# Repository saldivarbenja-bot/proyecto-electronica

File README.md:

# Sistema de Adquisicion y Acondicionamiento de Senales EMG

## Descripcion del proyecto

Este repositorio contiene el diseno de hardware y los archivos de fabricacion desarrollados para el proyecto de adquisicion de senales electromiograficas (EMG) de superficie. El objetivo es tomar los potenciales electricos generados por la actividad muscular, amplificarlos, filtrarlos mediante un circuito analogico y acondicionarlos para su posterior lectura segura mediante el convertidor analogo-digital (ADC) de un microcontrolador.

### Contexto y cambios respecto a la primera entrega

En la primera etapa del curso probamos el circuito en una protoboard. Aunque logramos captar senal, el montaje era muy inestable: los cables sueltos captaban demasiado ruido de 50 Hz de la red electrica y cualquier movimiento generaba falsos contactos o artefactos en la lectura.

Para esta segunda entrega trasladamos el circuito a una placa de circuito impreso (PCB) de una sola cara (capa inferior B.Cu), pensada para fabricarse mediante ruteo CNC en el laboratorio. Tambien anadimos zocalos y borneras para montar los componentes con firmeza y alimentar todo con dos baterias de 9V, lo que elimina el ruido de la red y previene riesgos electricos.

## Integrantes del grupo (Grupo 5)

* Marcelo de la Fuente (ma.delafuente@udd.cl)
* Benjamin Saldivar (b.saldivarb@udd.cl)
* Manuel Sepulveda (ma.sepulvedar@udd.cl)

Curso: Electronica Biomedica - Seccion 1
Carrera: Ingenieria Civil en Biomedicina
Universidad del Desarrollo

## Descripcion del circuito y componentes

El sistema cuenta con las siguientes etapas:

1. Captacion: Sensores de superficie conectados a un modulo Muscle Sensor V3 (o etapa equivalente de instrumentacion) que toma la diferencia de potencial muscular y atenua el ruido comun.
2. Acondicionamiento analogico: Dos amplificadores operacionales LM741 alimentados con fuente simetrica (+9V / -9V) encargados de ajustar la fase y la ganancia mediante resistencias de 15k, 8.2k y 10k ohmios.
3. Proteccion de entrada al microcontrolador: Un divisor de tension resistivo (18k y 10k ohmios) que reduce la salida maxima de 9V a menos de 3.3V, evitando sobrevoltajes en el microcontrolador.
4. Integracion con microcontrolador: Tiras de pines para montar una placa de desarrollo ESP32-S3 de 38 pines y facilitar la conexion de la senal acondicionada al ADC.
5. Alimentacion aislada: Dos baterias de 9V conectadas mediante borneras para generar +9V, -9V y tierra (GND).

### Lista de materiales

| Cantidad | Componente | Funcion | Encapsulado / Conexion |
| --- | --- | --- | --- |
| 1 | Modulo Advancer Muscle Sensor V3 | Captacion y pre-amplificacion EMG | Tira de pines hembra de 1x5 |
| 2 | Amplificadores operacionales LM741 | Inversion y ajuste de ganancia | DIP-8 con zocalo |
| 1 | ESP32-S3 (38 pines) | Socket de montaje | Dos tiras de pines de 1x19 |
| 4 | Resistencias de ganancia | Ajuste de ganancia (15k, 8.2k y dos de 10k) | Resistencias axiales Through-Hole |
| 2 | Resistencias divisor | Escalado a rango de 3.3V (18k y 10k) | Resistencias axiales Through-Hole |
| 2 | Borneras de 2 pines (5.08 mm) | Entrada de alimentacion desde baterias de 9V | Montaje en placa Through-Hole |

## Reglas de diseno de la placa (KiCad / CNC)

El ruteo de la placa se realizo respetando las limitaciones de fabricacion de la fresadora CNC del laboratorio:

* Capa de cobre: Ruteo realizado exclusivamente en la cara inferior (B.Cu).
* Ancho de pista minimo: 0.8 mm.
* Espaciado entre pistas (Clearance): 0.8 mm.
* Borde de la placa: Delimitado en la capa Edge.Cuts.
* Montaje: 4 perforaciones de 3.2 mm de diametro en las esquinas para fijar la placa.
* Serigrafia: Indicaciones claras para la polaridad de las baterias (+9V, GND, -9V), pin 1 de los circuitos integrados y nombres de conectores.

## Estructura de carpetas

El repositorio esta organizado de la siguiente manera:

```
├── README.md                      # Descripcion general del proyecto
├── docs/                          # Hojas de datos e informes de entrega
│   ├── datasheets/
│   └── entregables/
└── electronica/                   # Diseno esquematico y PCB
    ├── kicad/                     # Proyecto en KiCad (.kicad_pro, .kicad_sch, .kicad_pcb)
    ├── libraries/                 # Simbolos, huellas y modelos 3D locales
    └── outputs/                   # Archivos para fabricacion y revision
        ├── gerbers/               # Archivos Gerber y de perforacion (.zip)
        ├── schematic.pdf          # Esquema electronico en PDF
        ├── pcb_views/             # Vistas de pistas, render 3D y reporte DRC
        └── BOM.csv                # Lista de materiales exportada
```

## Como abrir y revisar el proyecto

### Abrir esquematicos y PCB en KiCad

1. Clona el repositorio o descarga el archivo ZIP:
   ```
   git clone <URL_DEL_REPOSITORIO>
   ```
2. Abre KiCad (version 7 o superior).
3. Ve a `Archivo > Abrir Proyecto` y selecciona el archivo `.kicad_pro` dentro de `electronica/kicad/`.
4. Las librerias de componentes y huellas estan guardadas de forma local en la carpeta `electronica/libraries/`, por lo que no presentaran dependencias externas faltantes.

## Referencias

* Informacion del sensor EMG: [Tutorial Sensor EMG - UNIT Electronics](https://blog.uelectronics.com/electronica/sensor-emg-tutorial-completo/)
* Circuito de ejemplo: [DIY Muscle Sensor / EMG Circuit - Instructables](https://www.instructables.com/Muscle-EMG-Sensor-for-a-Microcontroller/)
* Proyectos abiertos de referencia: [BioAmp EXG Pill](https://github.com/upsidedownlabs/BioAmp-EXG-Pill) y [Shield EKG-EMG de OLIMEX](https://www.olimex.com/Products/Duino/Shields/SHIELD-EKG-EMG/open-source-hardware)

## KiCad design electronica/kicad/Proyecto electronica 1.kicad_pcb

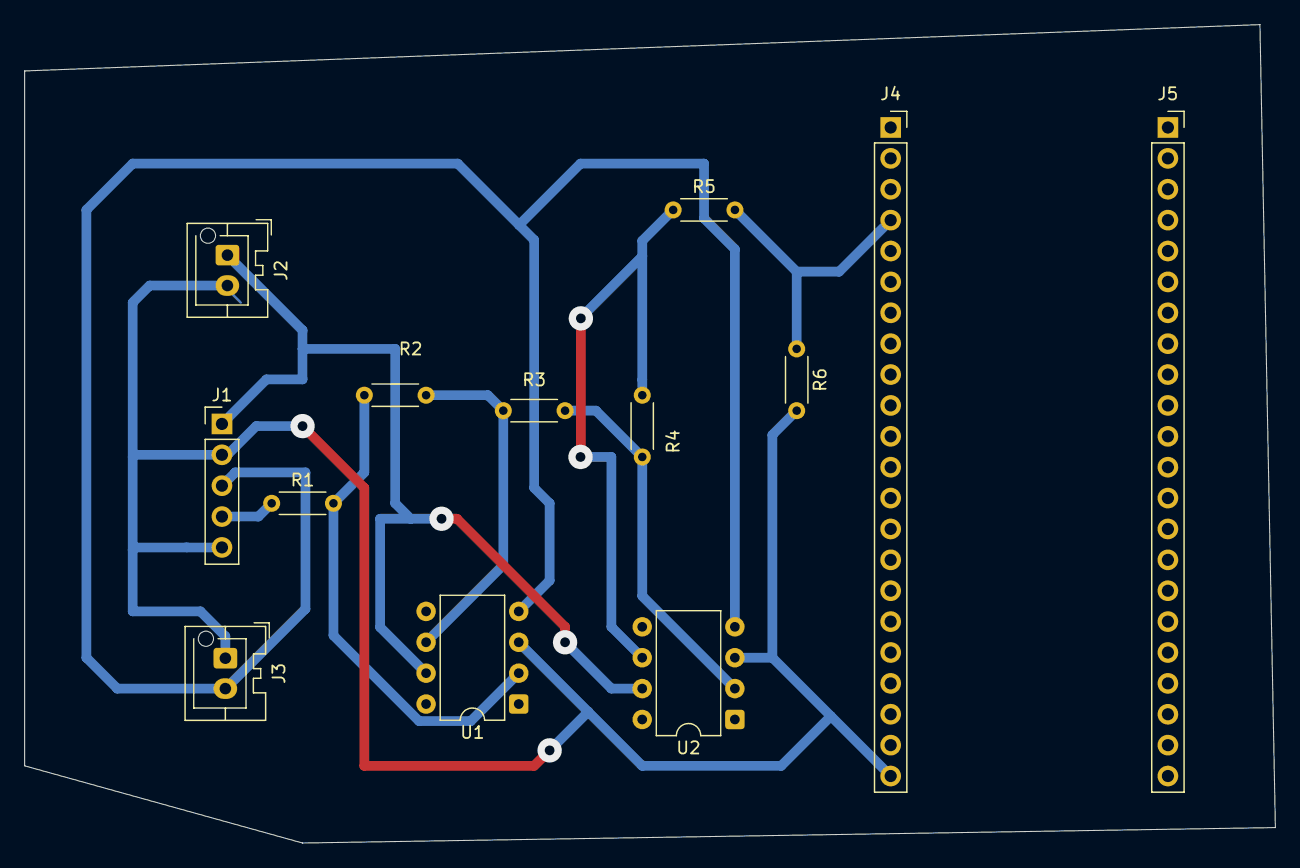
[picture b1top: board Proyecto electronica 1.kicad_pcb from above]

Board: 2 copper layers, 102.9 x 67.3 mm, 13 parts (0 on the bottom side), 9 nets.

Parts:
J1: Conn_01x05; PinHeader_1x05_P2.54mm_Vertical
J2, J3: Conn_01x02_Pin; JST_XA_B02B-XASK-1-A_1x02_P2.50mm_Vertical
J4, J5: Conn_01x22; PinSocket_1x22_P2.54mm_Vertical
R1, R2, R3, R4, R5, R6: R; R_Axial_DIN0204_L3.6mm_D1.6mm_P5.08mm_Horizontal
U1, U2: LM741; DIP-8_W7.62mm

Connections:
+9V: J1.1, J2.1, U1.7 (V+), U2.7 (V+)
-9V: J1.3, J3.2, U1.4 (V-), U2.4 (V-)
GND: J1.2, J1.5, J2.2, J3.1, J4.22, R6.2, U1.3 (+), U2.3 (+)
unnamed: J1.4, R1.1
unnamed: J4.4, R5.2, R6.1
unnamed: R2.2, R3.1, U1.6
unnamed: R4.2, R5.1, U2.6
unnamed: R1.2, R2.1, U1.2 (-)
unnamed: R3.2, R4.1, U2.2 (-)
